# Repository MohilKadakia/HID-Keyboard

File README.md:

# HID-Keyboard
Custom Low-Profile Keyboard using a Raspberry Pi Pico

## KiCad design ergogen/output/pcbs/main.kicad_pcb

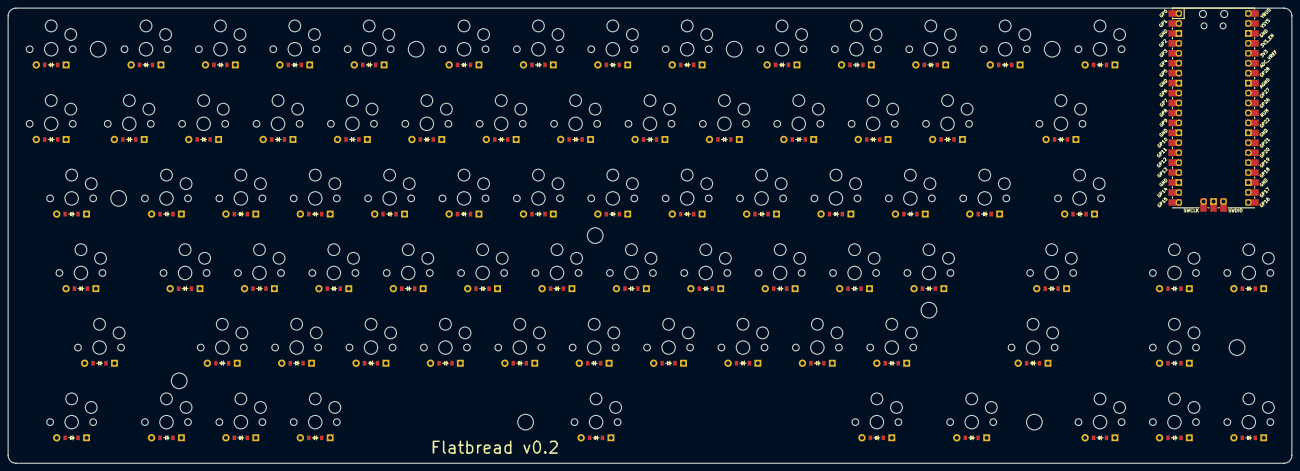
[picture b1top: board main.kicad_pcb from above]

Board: 2 copper layers, 327.9 x 116.2 mm, 162 parts (0 on the bottom side), 94 nets, no tracks yet.

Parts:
D1, D2, D3, D4, D5, D6, D7, D8, D9, D10, D11, D12, D13, D14, D15, D16, D17, D18, D19, D20, D21, D22, D23, D24, D25, D26, D27, D28, D29, D30, D31, D32, D33, D34, D35, D36, D37, D38, D39, D40, D41, D42, D43, D44, D45, D46, D47, D48, D49, D50, D51, D52, D53, D54, D55, D56, D57, D58, D59, D60, D61, D62, D63, D64, D65, D66, D67, D68, D69, D70, D71, D72, D73, D74, D75, D76, D77, D78, D79, D80: ComboDiode
S1, S2, S3, S4, S5, S6, S7, S8, S9, S10, S11, S12, S13, S14, S15, S16, S17, S18, S19, S20, S21, S22, S23, S24, S25, S26, S27, S28, S29, S30, S31, S32, S33, S34, S35, S36, S37, S38, S39, S40, S41, S42, S43, S44, S45, S46, S47, S48, S49, S50, S51, S52, S53, S54, S55, S56, S57, S58, S59, S60, S61, S62, S63, S64, S65, S66, S67, S68, S69, S70, S71, S72, S73, S74, S75, S76, S77, S78, S79, S80: PG1350
_1, _1#2: RPi_Pico_SMD_TH

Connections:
3V3: _1.36, _1#2.36
3V3_EN: _1.37, _1#2.37
ADC_VREF: _1.35, _1#2.35
AGND: _1.33, _1#2.33
GND: _1.3, _1.8, _1.13, _1.18, _1.23, _1.28, _1.38, _1#2.3, _1#2.8, _1#2.38
GP0: _1.1, _1#2.1
GP1: _1.2, _1#2.2
GP2: _1.4, _1#2.4
GP3: _1.5, _1#2.5
GP4: _1.6, _1#2.6
GP5: _1.7, _1#2.7
GP28: _1.34, _1#2.34
VBUS: _1.40, _1#2.40
VSYS: _1.39, _1#2.39
a_row: D44.2, S44.2
b_row: D63.2, S63.2
backslash_row: D42.2, S42.2
backspace_row: D14.2, S14.2
bottom_arrow_row: D79.2, S79.2
c_row: D61.2, S61.2
caps_row: D43.2, S43.2
comma_row: D66.2, S66.2
d_row: D46.2, S46.2
delete_row: D28.2, S28.2
e_row: D32.2, S32.2
enter_row: D55.2, S55.2
equal_row: D13.2, S13.2
escape_row: D15.2, S15.2
f1_row: D16.2, S16.2
f2_row: D17.2, S17.2
f3_row: D18.2, S18.2
f4_row: D19.2, S19.2
f5_row: D20.2, S20.2
f6_row: D21.2, S21.2
f7_row: D22.2, S22.2
f8_row: D23.2, S23.2
f9_row: D24.2, S24.2
f10_row: D25.2, S25.2
f11_row: D26.2, S26.2
f12_row: D27.2, S27.2
f_row: D47.2, S47.2
function_row: D72.2, S72.2
g_row: D48.2, S48.2
h_row: D49.2, S49.2
i_row: D37.2, S37.2
j_row: D50.2, S50.2
k_row: D51.2, S51.2
l_row: D52.2, S52.2
left_alt_row: D74.2, S74.2
left_arrow_row: D78.2, S78.2
left_control_row: D71.2, S71.2
left_shift_row: D58.2, S58.2
m_row: D65.2, S65.2
macro1_row: D56.2, S56.2
macro2_row: D57.2, S57.2
minus_row: D12.2, S12.2
n_row: D64.2, S64.2
num0_row: D11.2, S11.2
num1_row: D2.2, S2.2
num2_row: D3.2, S3.2
num3_row: D4.2, S4.2
num4_row: D5.2, S5.2
num5_row: D6.2, S6.2
num6_row: D7.2, S7.2
num7_row: D8.2, S8.2
num8_row: D9.2, S9.2
num9_row: D10.2, S10.2
o_row: D38.2, S38.2
p_row: D39.2, S39.2
period_row: D67.2, S67.2
q_row: D30.2, S30.2
quote_row: D54.2, S54.2
r_row: D33.2, S33.2
right_alt_row: D76.2, S76.2
right_arrow_row: D80.2, S80.2
right_control_row: D77.2, S77.2
right_shift_row: D69.2, S69.2
s_row: D45.2, S45.2
semicolon_row: D53.2, S53.2
slash_row: D68.2, S68.2
space_row: D75.2, S75.2
square_bracket_close_row: D41.2, S41.2
square_bracket_open_row: D40.2, S40.2
super_row: D73.2, S73.2
t_row: D34.2, S34.2
tab_row: D29.2, S29.2
tilda_row: D1.2, S1.2
u_row: D36.2, S36.2
up_arrow_row: D70.2, S70.2
v_row: D62.2, S62.2
w_row: D31.2, S31.2
x_row: D60.2, S60.2
y_row: D35.2, S35.2
z_row: D59.2, S59.2

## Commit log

2024-12-26 Ergogen Initial Commit
2024-12-26 Updated ergogen config - Added mounting holes - Added board text
2024-12-26 Case 3D Model - Added mounting points for M2 screws
2024-12-27 Moved mounting holes to make way for stabilizers - Stabilizer slots have been made in the faceplate outline
2024-12-27 Updated gitignore
